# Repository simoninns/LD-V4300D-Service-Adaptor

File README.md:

# LD-V4300D-Service-Adaptor
A service adaptor for the Pioneer LD-V4300D LaserDisc player

## Synopsis

This board is designed to assist with calibration of the Pioneer LD-V4300D LaserDisc player.  The board routes the various test signals to oscilloscope friendly terminals and also includes the passive components required for the service manual measurements.

## Motivation

Calibrating LD-V4300D players.

## Author

The LD-V4300D service adaptor board was designed by Simon Inns.

## License

This project is released under a Creative Commons Attribution-ShareAlike 4.0 International (CC BY-SA 4.0) licence.

You are free to:

Share  copy and redistribute the material in any medium or format
Adapt  remix, transform, and build upon the material
for any purpose, even commercially.

This license is acceptable for Free Cultural Works.

The licensor cannot revoke these freedoms as long as you follow the license terms.

Under the following terms:

Attribution  You must give appropriate credit, provide a link to the license,
and indicate if changes were made. You may do so in any reasonable manner, but
not in any way that suggests the licensor endorses you or your use.

ShareAlike  If you remix, transform, or build upon the material, you must
distribute your contributions under the same license as the original.

No additional restrictions  You may not apply legal terms or technological
measures that legally restrict others from doing anything the license permits.

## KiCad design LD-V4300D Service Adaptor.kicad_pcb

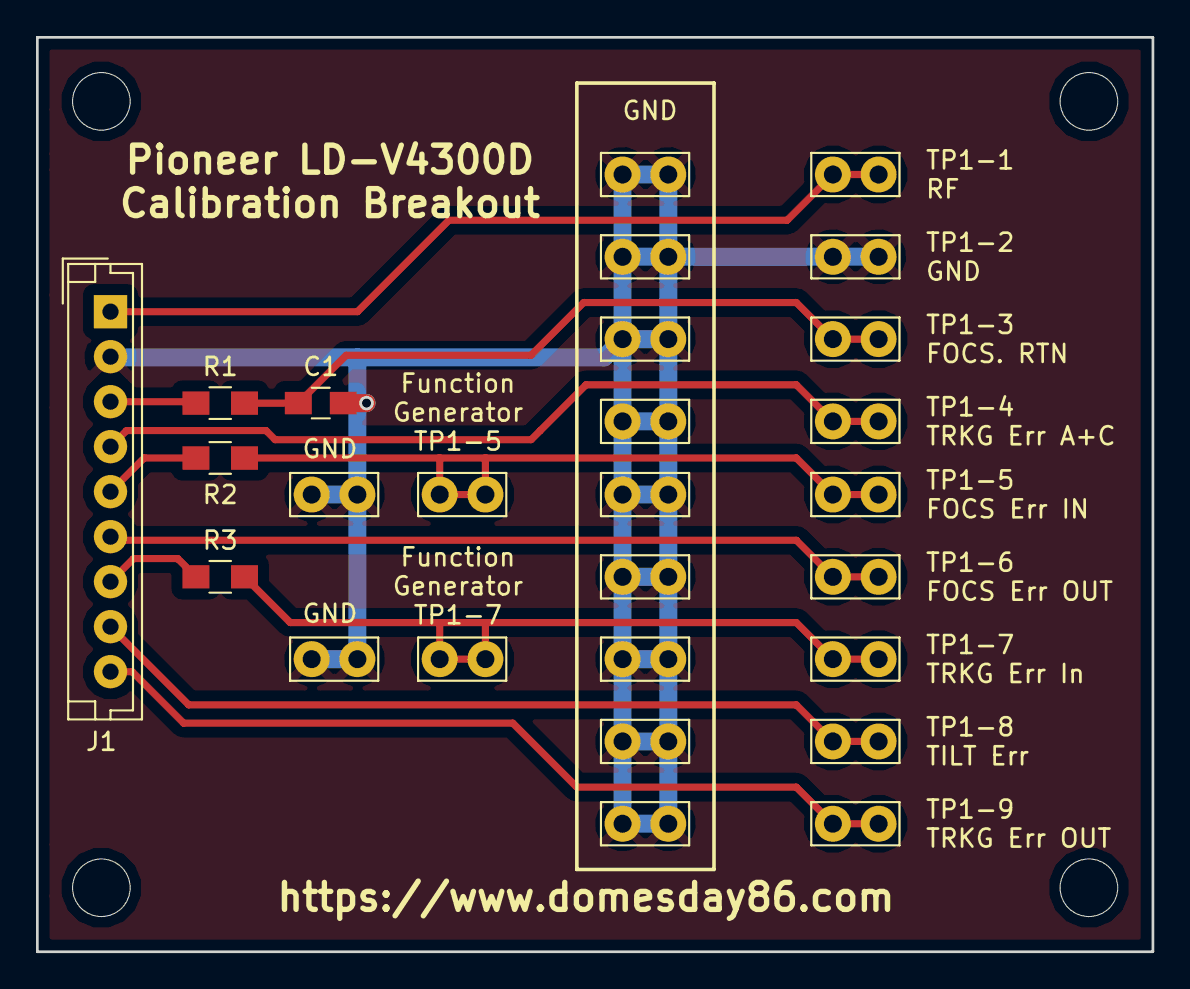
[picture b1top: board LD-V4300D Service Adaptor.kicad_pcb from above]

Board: 2 copper layers, 62.0 x 50.8 mm, 31 parts (0 on the bottom side), 12 nets.

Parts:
C1: 1uF; C_0805_HandSoldering
J1: Conn_01x09_Male; JST_EH_B09B-EH-A_09x2.50mm_Straight
MK1, MK2, MK3, MK4: Mounting_Hole; MountingHole_3.2mm_M3
R1, R2, R3: 100K; R_0805_HandSoldering
TP1, TP22: TP1-2 GND; Test_Point_Bridge_Pitch2.54mm_Drill1.0mm
TP2: TP1-1 RF; Test_Point_Bridge_Pitch2.54mm_Drill1.0mm
TP3: TP1-3 FOCS. RTN; Test_Point_Bridge_Pitch2.54mm_Drill1.0mm
TP4: TP1-4 TRKG Err A+C; Test_Point_Bridge_Pitch2.54mm_Drill1.0mm
TP5: TP1-5 FOCS Err IN; Test_Point_Bridge_Pitch2.54mm_Drill1.0mm
TP6: TP1-5 FG_in; Test_Point_Bridge_Pitch2.54mm_Drill1.0mm
TP7: TP1-5 FG GND; Test_Point_Bridge_Pitch2.54mm_Drill1.0mm
TP8: TP1-6 FOC Err OUT; Test_Point_Bridge_Pitch2.54mm_Drill1.0mm
TP9: TP1-7 TRKG Err In; Test_Point_Bridge_Pitch2.54mm_Drill1.0mm
TP10: TP1-7 FG_in; Test_Point_Bridge_Pitch2.54mm_Drill1.0mm
TP11: TP1-8 TILT Err; Test_Point_Bridge_Pitch2.54mm_Drill1.0mm
TP12: TP1-9 TRKG Err OUT; Test_Point_Bridge_Pitch2.54mm_Drill1.0mm
TP13: TP1-7 FG GND; Test_Point_Bridge_Pitch2.54mm_Drill1.0mm
TP14: TP1-1 GND; Test_Point_Bridge_Pitch2.54mm_Drill1.0mm
TP15: TP1-4 GND; Test_Point_Bridge_Pitch2.54mm_Drill1.0mm
TP16: TP1-6 GND; Test_Point_Bridge_Pitch2.54mm_Drill1.0mm
TP17: TP1-8 GND; Test_Point_Bridge_Pitch2.54mm_Drill1.0mm
TP18: TP1-3 GND; Test_Point_Bridge_Pitch2.54mm_Drill1.0mm
TP19: TP1-5 GND; Test_Point_Bridge_Pitch2.54mm_Drill1.0mm
TP20: TP1-7 GND; Test_Point_Bridge_Pitch2.54mm_Drill1.0mm
TP21: TP1-9 GND; Test_Point_Bridge_Pitch2.54mm_Drill1.0mm

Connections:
GND: C1.2, J1.2, TP1.1, TP7.1, TP13.1, TP14.1, TP15.1, TP16.1, TP17.1, TP18.1, TP19.1, TP20.1, TP21.1, TP22.1
unnamed: C1.1, R1.1, TP3.1
unnamed: J1.1, TP2.1
unnamed: J1.3, R1.2
unnamed: J1.4, TP4.1
unnamed: J1.5, R2.2
unnamed: J1.6, TP8.1
unnamed: J1.7, R3.2
unnamed: J1.8, TP11.1
unnamed: J1.9, TP12.1
unnamed: R2.1, TP5.1, TP6.1
unnamed: R3.1, TP9.1, TP10.1

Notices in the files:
LD-V4300D Service Adaptor.kicad_pcb:
(c)2018 Simon Inns
License: Attribution-ShareAlike International (CC BY-SA 4.0)
(c)2018 Simon Inns - CC BY-SA 4.0
